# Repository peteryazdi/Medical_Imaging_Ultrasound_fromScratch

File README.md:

# Multi-Channel Ultrasound Imaging Device

## Overview

This repository documents the design and development of a custom ultrasound imaging platform. The system progresses from a single-channel 5 MHz analog front end to a multi-channel digital beamforming system capable of acquiring raw RF echo data, processing it on an FPGA, and producing ultrasound images.

The project covers transducer characterization, high-voltage pulse generation, low-noise receive electronics, analog-to-digital conversion, and FPGA-based signal processing.

---

## Current Status

**Rev 0 complete. Rev 1 schematic complete — PCB layout in progress.**

### Completed

- Two 5 MHz thickness-gauge transducers purchased and characterized
- Center frequency confirmed at 5.000 MHz via oscilloscope cursor measurement
- Both channels verified functional using AD2 impulse excitation
- Ring-down and cross-coupling observed through gel-coupled water path
- Rev 1 8-channel Tx/Rx schematic designed and ERC-clean in KiCad

### Rev 1 Hardware Design

The Rev 1 board is an 8-channel transmit pulser with passive receive protection, designed around the MD1213 gate driver and TC6320 complementary MOSFET pair (Microchip).

**Per channel:**
- MD1213 dual MOSFET gate driver (VQFN-12, ±5V bipolar supply)
- TC6320 N+P MOSFET pair (SOIC-8, 200V BVDSS)
- 10nF/200V AC coupling capacitors (OUTA→GP, OUTB→GN)
- 1μF/200V storage capacitors per HV rail with 1MΩ bleed resistors
- 0.47μF/16V bypass capacitors on ±5V driver supply
- Back-to-back clamp diodes (300V rated) for Tx protection
- 200Ω series resistor + back-to-back clamp diodes to GND for Rx protection
- 1MΩ DC bias resistor on Tx/Rx node
- 10kΩ pull-down on OE (outputs disabled by default)
- SMA vertical connector per channel (SMA-to-Lemo adapter for current transducers)

**Power supply (bench supply fed via screw terminals):**
- ±100V HV rails: 10μF electrolytic + 1μF ceramic + 1MΩ bleed per rail
- ±5V LV rails: 10μF ceramic per rail
- Dedicated GND screw terminal

**Control and I/O:**
- 2×14 pin header for FPGA connection (8× INA, INB, OE + TRIG_OUT, TRIG_IN, GND)
- 33Ω series resistors on all logic inputs
- 2×8 pin header for Rx output (8 channels with alternating GND pins)
- LED indicators: +5V power (green), +100V power (red), trigger activity (yellow), OE status (blue)

---

## Key Specifications

| Parameter | Value |
|---|---|
| Transducer frequency | 5 MHz |
| Pulse type | Bipolar, 1 cycle (200 ns) |
| HV supply range | ±5V to ±100V (variable via bench supply) |
| Number of Tx/Rx channels | 8 |
| MOSFET breakdown voltage | 200V (TC6320) |
| Gate drive swing | ±5V (10V total, AC coupled) |
| Rise time (500pF load) | ~8 ns |
| Peak current (100V, 7Ω RDS) | 14.3A instantaneous |
| Rx clamp voltage | ±0.7V |
| Dead zone (200Ω Rx series) | < 0.1 mm |
| Max imaging depth at 7700 Hz PRF | 10 cm |
| Axial resolution (theoretical) | 0.154 mm |
| Power dissipation per TC6320 | ~17 mW |

---

## Development Roadmap

| Revision | Scope | Status |
|---|---|---|
| Rev 0 | Transducer characterization, initial impulse testing | Complete |
| Rev 1 | 8-channel Tx pulser + passive Rx protection, scope-based echo measurement | Schematic complete, PCB layout in progress |
| Rev 2 | Multi-channel Rx analog chain (LNA, bandpass filter, TGC) on separate board | Planned |
| Rev 3 | ADC integration, digitization of RF echo data | Planned |
| Rev 4 | FPGA DSP pipeline: filtering, envelope detection, delay-and-sum beamforming | Planned |
| Rev 5 | A-scan and B-scan visualization, phantom imaging | Planned |

---

## Hardware

### Transducers
- 5 MHz thickness-gauge transducers (Amazon, 2 units)
- Lemo connectors, connected via SMA-to-Lemo adapter cables
- Used for both Tx and Rx in pitch-catch configuration

### Test Equipment
- Digilent Analog Discovery 2 (AD2) — initial low-voltage impulse source
- Tektronix TDS 2014 oscilloscope — waveform capture and measurement
- Ultrasound coupling gel

---

## Physics Reference

| Quantity | Formula | Value at 5 MHz |
|---|---|---|
| Wavelength | λ = c / f | 0.308 mm |
| Axial resolution | c / (2f) per cycle | 0.154 mm |
| Depth from echo time | d = ct / 2 | 0.77 mm/μs |
| Max PRF | c / (2 × d_max) | 7700 Hz at 10 cm |
| Attenuation | ~0.5 dB/cm/MHz | 2.5 dB/cm |
| Sound speed (soft tissue) | — | 1540 m/s |

---

## Safety

This is an educational project, not a certified medical device. The system is not intended for diagnostic or clinical use. High-voltage circuits require appropriate safety practices. All testing is performed on phantoms, water-path setups, and non-clinical targets.

---

## Author

Peter Yazdi — peteryazdi@gmail.com

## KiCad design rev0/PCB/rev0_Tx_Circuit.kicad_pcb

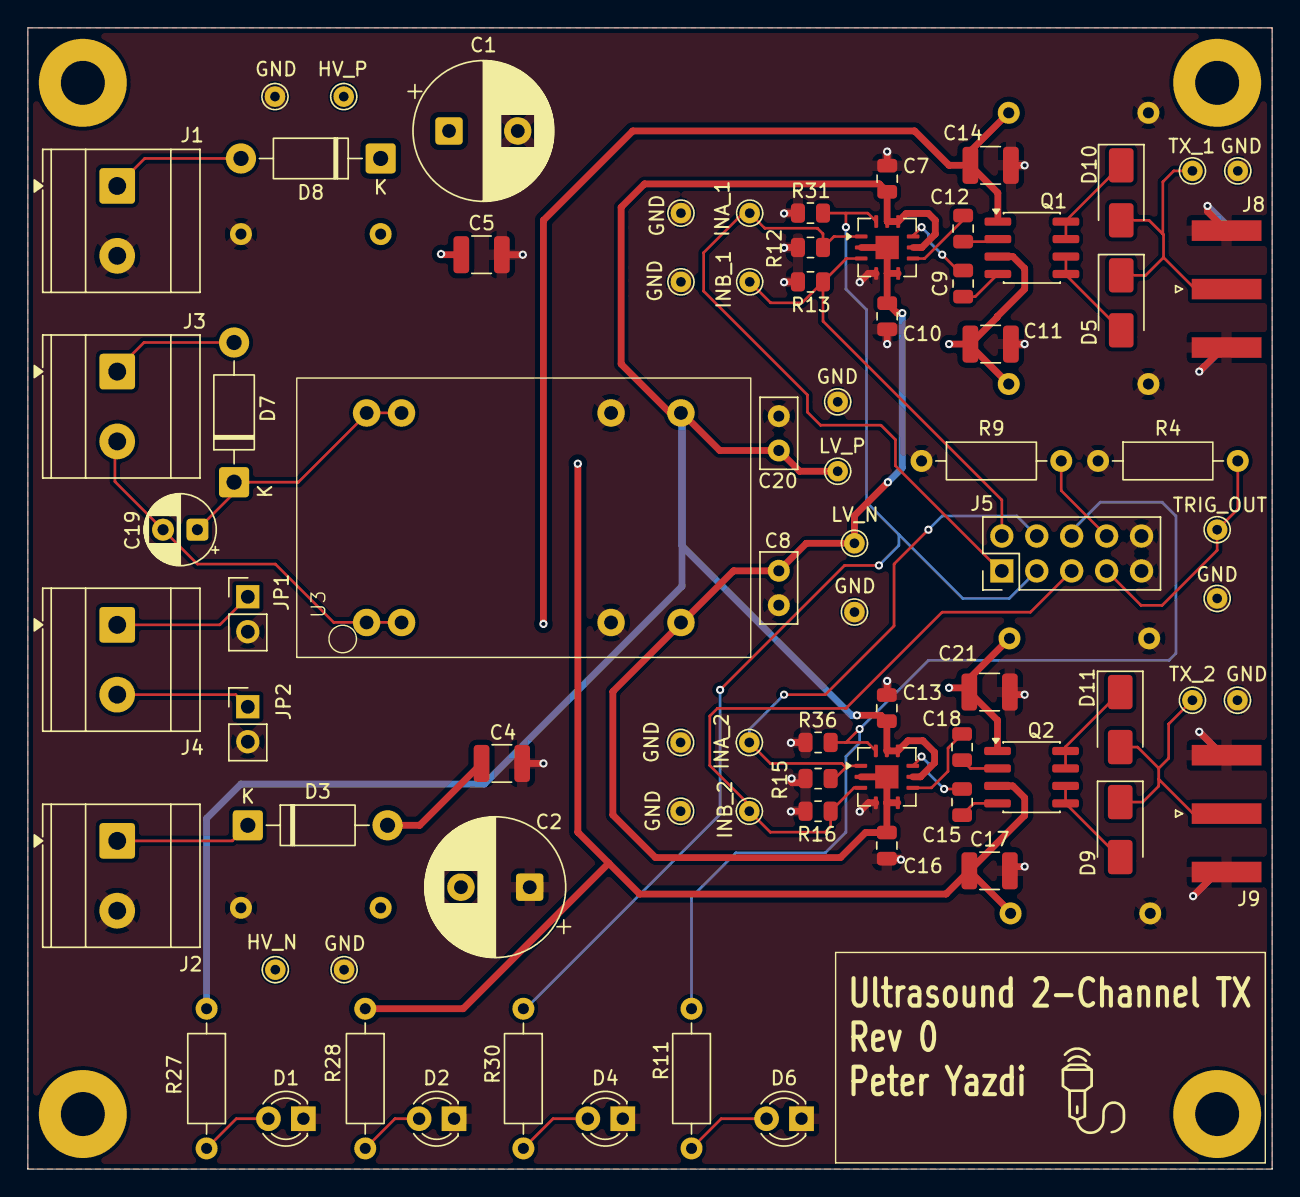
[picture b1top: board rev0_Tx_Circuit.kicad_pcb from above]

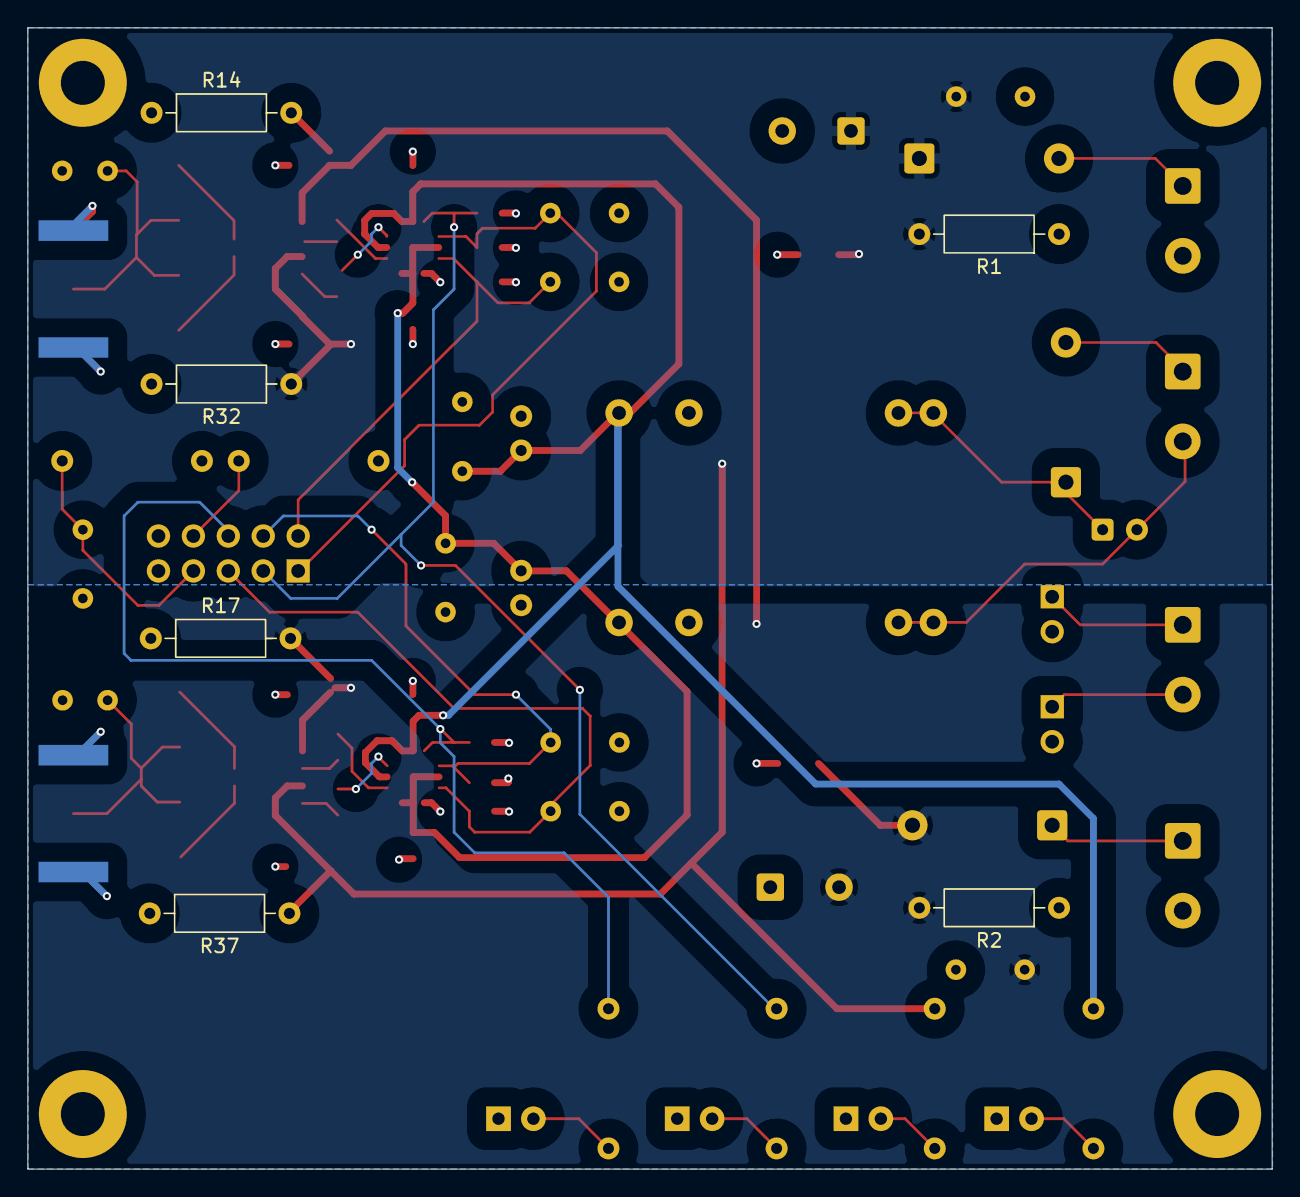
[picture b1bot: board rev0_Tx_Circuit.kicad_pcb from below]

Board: 4 copper layers, 90.5 x 83.0 mm, 84 parts (6 on the bottom side), 38 nets.

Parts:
C1, C2: 10uF/200V; CP_Radial_D10.0mm_P5.00mm
C4, C5: 1uF / 200V; C_1210_3225Metric
C7, C10, C13, C16: 0.47uF/50V; C_0805_2012Metric
C8: 1ufF / 16V; C_Disc_D5.0mm_W2.5mm_P2.50mm
C9, C12, C15, C18: 10nF/200V; C_0805_2012Metric
C11, C14, C17, C21: 1uF/250V; C_1210_3225Metric
C19: 10uF/16V; CP_Radial_D5.0mm_P2.50mm
C20: 1uF / 16V; C_Disc_D5.0mm_W2.5mm_P2.50mm
D1, D4, D6: LED_GREEN; LED_D3.0mm
D2: LED_RED; LED_D3.0mm
D3, D8: 1N4007; D_DO-41_SOD81_P10.16mm_Horizontal
D5, D9, D10, D11: MURS160; D_SMA
D7: 1N5819; D_DO-41_SOD81_P10.16mm_Horizontal
GND: GND; TestPoint_THTPad_D1.5mm_Drill0.7mm
GND#2, GND#3, GND#4, GND#5, GND#6, GND#7, GND#8, GND#9, GND#10, GND#11: GND; TestPoint_THTPad_D1.5mm_Drill0.7mm
HV_N: HV_N; TestPoint_THTPad_D1.5mm_Drill0.7mm
HV_P: HV_P; TestPoint_THTPad_D1.5mm_Drill0.7mm
INA_1, INA_2: INA; TestPoint_THTPad_D1.5mm_Drill0.7mm
INB_1, INB_2: INB; TestPoint_THTPad_D1.5mm_Drill0.7mm
J1, J2, J3, J4: Screw_Terminal_01x02; TerminalBlock_Phoenix_MKDS-3-2-5.08_1x02_P5.08mm_Horizontal
J5: Conn_02x05_Odd_Even; PinHeader_2x05_P2.54mm_Vertical
J8, J9: SMA Vertical; SMA_Amphenol_132289_EdgeMount
JP1, JP2: Jumper_2pin; PinHeader_1x02_P2.54mm_Vertical
LV_N: DRV_N5V; TestPoint_THTPad_D1.5mm_Drill0.7mm
LV_P: DRV_P5V; TestPoint_THTPad_D1.5mm_Drill0.7mm
Q1, Q2: TC6320; SOIC-8_3.9x4.9mm_P1.27mm
R1, R2, R14, R17, R32, R37: 1M / 0.25W; R_Axial_DIN0207_L6.3mm_D2.5mm_P10.16mm_Horizontal
R4, R9: 10K; R_Axial_DIN0207_L6.3mm_D2.5mm_P10.16mm_Horizontal
R11, R27, R30: 470 ohm, 0.25W; R_Axial_DIN0207_L6.3mm_D2.5mm_P10.16mm_Horizontal
R12, R13, R15, R16, R31, R36: 10K; R_0805_2012Metric
R28: 100K, 0.25W; R_Axial_DIN0207_L6.3mm_D2.5mm_P10.16mm_Horizontal
TRIG_OUT: TRIG_OUT; TestPoint_THTPad_D1.5mm_Drill0.7mm
TX_1: TX_Node_1; TestPoint_THTPad_D1.5mm_Drill0.7mm
TX_2: TX_Node_2; TestPoint_THTPad_D1.5mm_Drill0.7mm
U1, U2: MD1213; MD1213_VQFN12_4x4_P0.8_EP1.7x1.7
U3: DCWN03_05; DCWN03_DIP24_8PIN

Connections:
/CONTROL_IO/CH1_INA: INA_1.1 (1_1), J5.1, R12.1, U1.1 (INA)
/CONTROL_IO/CH1_INB: INB_1.1 (1_1), J5.2, R13.2, U1.3 (INB)
/CONTROL_IO/CH1_OE: J5.3, R30.1, R31.1, U1.12 (OE)
/CONTROL_IO/CH2_INA: INA_2.1 (1_1), J5.4, R15.1, U2.1 (INA)
/CONTROL_IO/CH2_INB: INB_2.1 (1_1), J5.5, R16.2, U2.3 (INB)
/CONTROL_IO/CH2_OE: J5.6, R11.1, R36.1, U2.12 (OE)
/CONTROL_IO/TRIG_IN: J5.8, R9.2
/CONTROL_IO/TX_Node_1: D5.1 (K), D10.2 (A), J8.1 (In), TX_1.1 (1_1)
/CONTROL_IO/TX_Node_2: D9.1 (K), D11.2 (A), J9.1 (In), TX_2.1 (1_1)
DRV_N5V: C8.1, C10.2, C16.2, LV_N.1 (1_1), U1.2 (VL), U1.5 (VSS1), U1.6 (VSS2), U1.13 (EP), U2.2 (VL), U2.5 (VSS1), U2.6 (VSS2), U2.13 (EP), U3.11 (-Vout)
DRV_P5V: C7.1, C13.1, C20.2, LV_P.1 (1_1), R27.1, U1.8 (VH), U1.10 (VDD2), U1.11 (VDD1), U2.8 (VH), U2.10 (VDD2), U2.11 (VDD1), U3.14 (+Vout)
GND: C1.2, C2.1, C4.1, C5.1, C7.2, C8.2, C10.1, C11.2, C13.2, C14.1, C16.1, C17.2, C20.1, C21.1, D1.1 (K), D2.1 (K), D4.1 (K), D6.1 (K), GND.1 (1_1), GND#2.1 (1_1), GND#3.1 (1_1), GND#4.1 (1_1), GND#5.1 (1_1), GND#6.1 (1_1), GND#7.1 (1_1), GND#8.1 (1_1), GND#9.1 (1_1), GND#10.1 (1_1), GND#11.1 (1_1), J1.2, J2.2, J5.9, J5.10, J8.2 (Ext), J9.2 (Ext), JP1.2 (B), JP2.2 (B), R1.1, R2.1, R4.1, R9.1, R12.2, R13.1, R14.1, R15.2, R16.1, R17.1, R31.2, R32.2, R36.2, R37.2, U1.4 (GND), U2.4 (GND), U3.9 (Common), U3.16 (Common)
HV_N: C2.2, C4.2, C14.2, C21.2, D3.2 (A), HV_N.1 (1_1), Q1.1 (SN), Q2.1 (SN), R2.2, R14.2, R17.2
HV_P: C1.1, C5.2, C11.1, C17.1, D8.1 (K), HV_P.1 (1_1), Q1.3 (SP), Q2.3 (SP), R1.2, R28.1, R32.1, R37.1
unnamed: D1.2 (A), R27.2
unnamed: D2.2 (A), R28.2
unnamed: D3.1 (K), J2.1
unnamed: D4.2 (A), R30.2
unnamed: D5.2 (A), Q1.5 (DP), Q1.6 (DP)
unnamed: D6.2 (A), R11.2
unnamed: D7.2 (A), J3.1
unnamed: C19.1, D7.1 (K), U3.22 (+Vin), U3.23 (+Vin)
unnamed: D8.2 (A), J1.1
unnamed: D9.2 (A), Q2.5 (DP), Q2.6 (DP)
unnamed: D10.1 (K), Q1.7 (DN), Q1.8 (DN)
unnamed: D11.1 (K), Q2.7 (DN), Q2.8 (DN)
unnamed: C19.2, J3.2, U3.2 (-Vin), U3.3 (-Vin)
unnamed: J4.1, JP1.1 (A)
unnamed: J4.2, JP2.1 (A)
unnamed: J5.7, R4.2, TRIG_OUT.1 (1_1)
unnamed: C12.2, Q1.2 (GN)
unnamed: C9.2, Q1.4 (GP)
unnamed: C18.2, Q2.2 (GN)
unnamed: C15.2, Q2.4 (GP)
unnamed: C9.1, U1.9 (OUTA)
unnamed: C12.1, U1.7 (OUTB)
unnamed: C15.1, U2.9 (OUTA)
unnamed: C18.1, U2.7 (OUTB)

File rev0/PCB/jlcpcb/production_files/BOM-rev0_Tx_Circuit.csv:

Comment,Designator,Footprint,LCSC,Quantity
LED_GREEN,D4,LED_D3.0mm,,1
SMA Vertical,J8,SMA_Amphenol_132134-10_Vertical,,1
"470 ohm, 0.25W",R11,R_Axial_DIN0207_L6.3mm_D2.5mm_P10.16mm_Horizontal,,1
GND,INB_GND_TP2,TestPoint_THTPad_D1.5mm_Drill0.7mm,,1
TX_Node_1,TX_1_TP1,TestPoint_THTPad_D1.5mm_Drill0.7mm,,1
TC6320,Q2,SOIC-8_3.9x4.9mm_P1.27mm,,1
GND,TRIG_OUT_GND_TP1,TestPoint_THTPad_D1.5mm_Drill0.7mm,,1
LED_GREEN,D1,LED_D3.0mm,,1
LED_GREEN,D6,LED_D3.0mm,,1
HV_N,HV_N_TP1,TestPoint_THTPad_D1.5mm_Drill0.7mm,,1
1N5819,D7,D_DO-41_SOD81_P10.16mm_Horizontal,,1
1uF / 200V,C4,C_1210_3225Metric,,1
"470 ohm, 0.25W",R27,R_Axial_DIN0207_L6.3mm_D2.5mm_P10.16mm_Horizontal,,1
Jumper_2pin,JP2,PinHeader_1x02_P2.54mm_Vertical,,1
"100K, 0.25W",R28,R_Axial_DIN0207_L6.3mm_D2.5mm_P10.16mm_Horizontal,,1
HV_P,HV_P_TP1,TestPoint_THTPad_D1.5mm_Drill0.7mm,,1
INB,INB_TP2,TestPoint_THTPad_D1.5mm_Drill0.7mm,,1
1uF/250V,C11,C_1210_3225Metric,,1
DRV_P5V,LV_P_TP1,TestPoint_THTPad_D1.5mm_Drill0.7mm,,1
TC6320,Q1,SOIC-8_3.9x4.9mm_P1.27mm,,1
10K,R16,R_0805_2012Metric,,1
10K,R9,R_Axial_DIN0207_L6.3mm_D2.5mm_P10.16mm_Horizontal,,1
10K,R36,R_0805_2012Metric,,1
GND,INA_GND_TP2,TestPoint_THTPad_D1.5mm_Drill0.7mm,,1
MURS160,D5,D_SMA,,1
Screw_Terminal_01x02,J3,TerminalBlock_Phoenix_MKDS-3-2-5.08_1x02_P5.08mm_Horizontal,,1
Screw_Terminal_01x02,J1,TerminalBlock_Phoenix_MKDS-3-2-5.08_1x02_P5.08mm_Horizontal,,1
1uF/250V,C14,C_1210_3225Metric,,1
Jumper_2pin,JP1,PinHeader_1x02_P2.54mm_Vertical,,1
10uF/16V,C19,CP_Radial_D5.0mm_P2.50mm,,1
1uF/250V,C17,C_1210_3225Metric,,1
10nF/200V,C15,C_0805_2012Metric,,1
10K,R13,R_0805_2012Metric,,1
MURS160,D10,D_SMA,,1
Conn_02x05_Odd_Even,J5,PinHeader_2x05_P2.54mm_Vertical,,1
10nF/200V,C9,C_0805_2012Metric,,1
TX_Node_2,TX_2_TP1,TestPoint_THTPad_D1.5mm_Drill0.7mm,,1
10nF/200V,C12,C_0805_2012Metric,,1
10K,R12,R_0805_2012Metric,,1
DCWN03_05,U3,DCWN03_DIP24_8PIN,,1
10uF/200V,C1,CP_Radial_D10.0mm_P5.00mm,,1
DRV_N5V,LV_N_TP1,TestPoint_THTPad_D1.5mm_Drill0.7mm,,1
10uF/200V,C2,CP_Radial_D10.0mm_P5.00mm,,1
SMA Vertical,J9,SMA_Amphenol_132134-10_Vertical,,1
TRIG_OUT,TRIG_OUT_TP1,TestPoint_THTPad_D1.5mm_Drill0.7mm,,1
INB,INB_TP1,TestPoint_THTPad_D1.5mm_Drill0.7mm,,1
INA,INA_TP2,TestPoint_THTPad_D1.5mm_Drill0.7mm,,1
GND,INB_GND_TP1,TestPoint_THTPad_D1.5mm_Drill0.7mm,,1
MD1213,U1,MD1213_VQFN12_4x4_P0.8_EP1.7x1.7,,1
0.47uF/50V,C16,C_0805_2012Metric,,1
1uF/250V,C21,C_1210_3225Metric,,1
GND,INA_GND_TP1,TestPoint_THTPad_D1.5mm_Drill0.7mm,,1
10nF/200V,C18,C_0805_2012Metric,,1
GND,TX_2_GND_TP1,TestPoint_THTPad_D1.5mm_Drill0.7mm,,1
MD1213,U2,MD1213_VQFN12_4x4_P0.8_EP1.7x1.7,,1
1N4007,D8,D_DO-41_SOD81_P10.16mm_Horizontal,,1
10K,R4,R_Axial_DIN0207_L6.3mm_D2.5mm_P10.16mm_Horizontal,,1
GND,LV_N_GND_TP1,TestPoint_THTPad_D1.5mm_Drill0.7mm,,1
GND,HV_P_GND_TP1,TestPoint_THTPad_D1.5mm_Drill0.7mm,,1
0.47uF/50V,C7,C_0805_2012Metric,,1
INA,INA_TP1,TestPoint_THTPad_D1.5mm_Drill0.7mm,,1
10K,R31,R_0805_2012Metric,,1
Screw_Terminal_01x02,J4,TerminalBlock_Phoenix_MKDS-3-2-5.08_1x02_P5.08mm_Horizontal,,1
MURS160,D9,D_SMA,,1
1N4007,D3,D_DO-41_SOD81_P10.16mm_Horizontal,,1
0.47uF/50V,C10,C_0805_2012Metric,,1
GND,TX_1_GND_TP1,TestPoint_THTPad_D1.5mm_Drill0.7mm,,1
LED_RED,D2,LED_D3.0mm,,1
"470 ohm, 0.25W",R30,R_Axial_DIN0207_L6.3mm_D2.5mm_P10.16mm_Horizontal,,1
1ufF / 16V,C8,C_Disc_D5.0mm_W2.5mm_P2.50mm,,1
Screw_Terminal_01x02,J2,TerminalBlock_Phoenix_MKDS-3-2-5.08_1x02_P5.08mm_Horizontal,,1
0.47uF/50V,C13,C_0805_2012Metric,,1
1uF / 200V,C5,C_1210_3225Metric,,1
GND,HV_N_GND_TP1,TestPoint_THTPad_D1.5mm_Drill0.7mm,,1
MURS160,D11,D_SMA,,1
1uF / 16V,C20,C_Disc_D5.0mm_W2.5mm_P2.50mm,,1
10K,R15,R_0805_2012Metric,,1
GND,LV_P_GND_TP1,TestPoint_THTPad_D1.5mm_Drill0.7mm,,1
1M / 0.25W,R2,R_Axial_DIN0207_L6.3mm_D2.5mm_P10.16mm_Horizontal,,1
1M / 0.25W,R14,R_Axial_DIN0207_L6.3mm_D2.5mm_P10.16mm_Horizontal,,1
1M / 0.25W,R32,R_Axial_DIN0207_L6.3mm_D2.5mm_P10.16mm_Horizontal,,1
1M / 0.25W,R17,R_Axial_DIN0207_L6.3mm_D2.5mm_P10.16mm_Horizontal,,1
1M / 0.25W,R37,R_Axial_DIN0207_L6.3mm_D2.5mm_P10.16mm_Horizontal,,1
1M / 0.25W,R1,R_Axial_DIN0207_L6.3mm_D2.5mm_P10.16mm_Horizontal,,1

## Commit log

2026-03-04 Initial plan
2026-03-04 Implement 16-channel phased-array ultrasound imaging system
2026-03-16 readme start
2026-03-16 Update main README with project structure and roadmap
2026-03-16 Initialize main branch repository structure
2026-03-16 Initialize theory branch structure
2026-04-11 rev0_hardware
2026-04-11 readme
2026-06-06 rev0 PCB in progress
2026-06-06 Restore project files; reorganize Rev0 PCB layout, add JLC production files
2026-06-06 Remove old rev0_Tx_Circuit folder
